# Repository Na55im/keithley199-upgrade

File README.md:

# Keithley 199 Digital Board Replacement

**Collaboration:** [keithley199-upgrade](https://github.com/Na55im/keithley199-upgrade) on GitHub (branch `main`).

This is an upgrade replacement for the digital control board on Keithley 199 multimeters.

The [Keithley 199](doc/k199_op_maint.pdf) is a digital multimeter built in the nineties. It is capable of current, voltage and resistance measurements and also provides a gpib interface for remote control.

These multimeters contains three electronic circuit boards, one which contains the analog circuitry, including analog signal conditioning and analog digital converter, a display board which contains the user interface, and a digital control board, with a processor who controls display, gpib interface and analog digital converter.

This repository contains hardware and software files needed to build a replacement of the digital control board.

# Features
- Voltage Measurement 0.3, 3, 30, 300 VDC/VAC 6.5 digits
- Current Measurement 30mA, 3A DC/AC,  6.5 digits
- Resistance Measurement 300-3GOhm, 6.5 digits, 4 wire.
- Arbitrary integration period
- SCPI interface
- Free Software

# Building the hardware 

The hardware files are in [Kicad](http://kicad-pcb.org/) format. Gerber files are (not yet) available.

# Building the software

The software was built with the [Microchip Toolchain](http://www.microchip.com/mplab/compilers). 

We use [Ceedling](http://www.throwtheswitch.org/ceedling/) for building and testing (but for comfort, [MPLABX](http://www.microchip.com/mplab/mplab-x-ide) files are available). 

In order to build the software, go to the root directory and do:

```
$rake release

```
Or to perform the unit tests:
```
$rake test:all
```

## Hardware

The hardware is pretty basic. It contains a pic32mx controller which do the heavy lifting. An ftdi chip provides an usb interface, while two open drain drivers controll the led displays. The external trigger input and output are connected to the microcontroller through the necessary input/output protection.

## Calibration

TODO

## Principles of Operation

The interesting part is the Control of the analog board. The analog board contains a series of switches that are controlled with a shift register. The adc conversion is performed with a discrete charge-balance adc which returns a pulse train with a pulse count proportional to the input voltage. The control of the adc is performed by the microcontroller in the digital board and should observe a precise timing in order to guarantee adc accuracy.

As shown in the figure above, the charge balance phase starts after the controller sends a start of conversion to the analog board. While the charge balance phase takes place, the controller counts the number of pulses it receives from the analog board. The analog board only send pulses on the up parts, thus the number of pulses is proportional to the charge acumulated. After exactly 16.66 msecs the controller sends an stop of conversion and the single slope phase starts, discharging the integrator. While discharge takes place, the controller counts the number of pulses received.

# Licence

```
 * Copyright (c) 2015, Diego F. Asanza. All rights reserved.
 *
 * This software is free software; you can redistribute it and/or
 * modify it under the terms of the GNU Lesser General Public
 * License as published by the Free Software Foundation; either
 * version 2.1 of the License, or (at your option) any later version.
 *
 * This library is distributed in the hope that it will be useful,
 * but WITHOUT ANY WARRANTY; without even the implied warranty of
 * MERCHANTABILITY or FITNESS FOR A PARTICULAR PURPOSE.  See the GNU
 * Lesser General Public License for more details.
 *
 * You should have received a copy of the GNU Lesser General Public
 * License along with this library; if not, write to the Free Software
 * Foundation, Inc., 51 Franklin Street, Fifth Floor, Boston,
 * MA 02110-1301  USA
 *
 ```

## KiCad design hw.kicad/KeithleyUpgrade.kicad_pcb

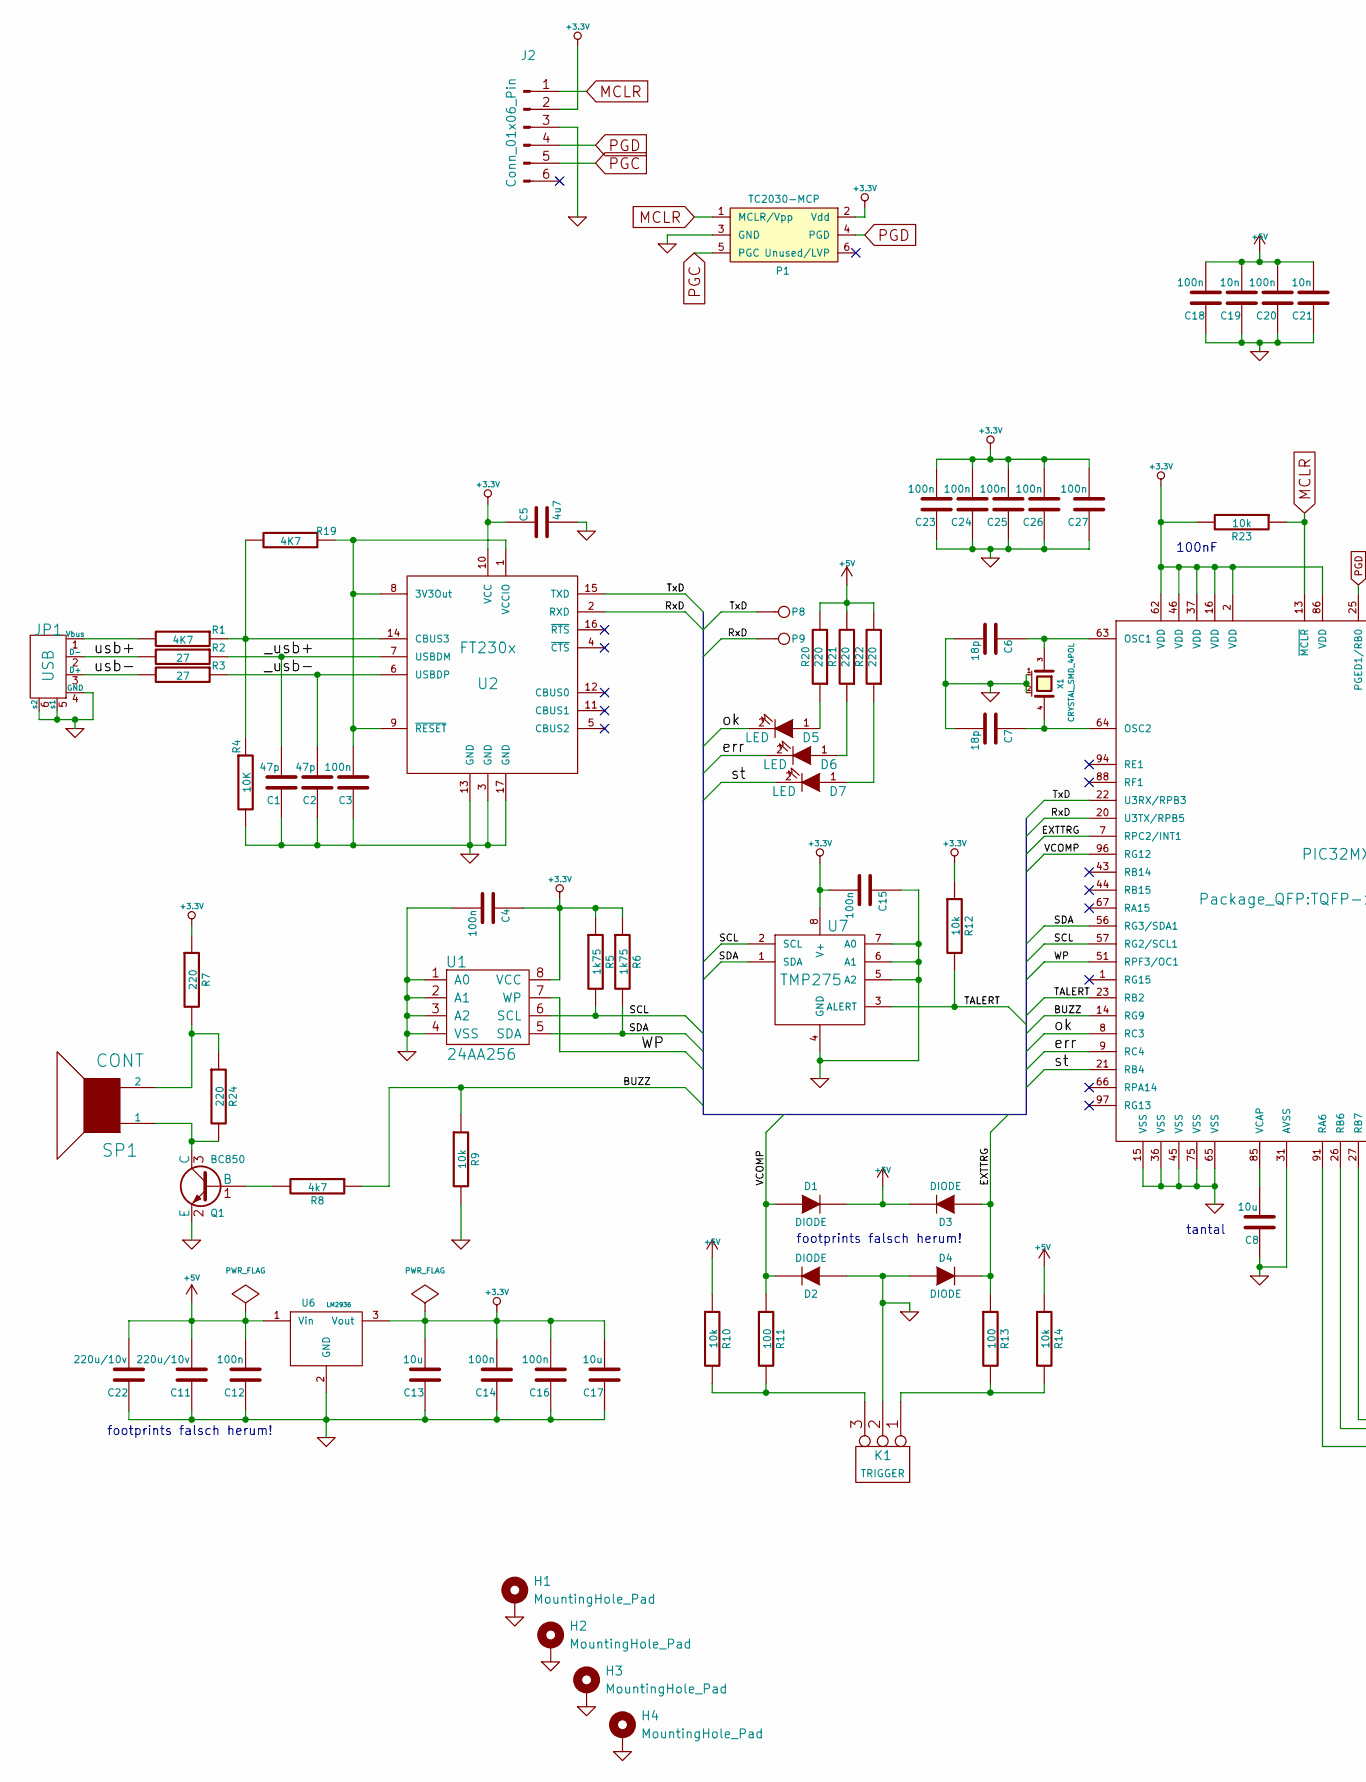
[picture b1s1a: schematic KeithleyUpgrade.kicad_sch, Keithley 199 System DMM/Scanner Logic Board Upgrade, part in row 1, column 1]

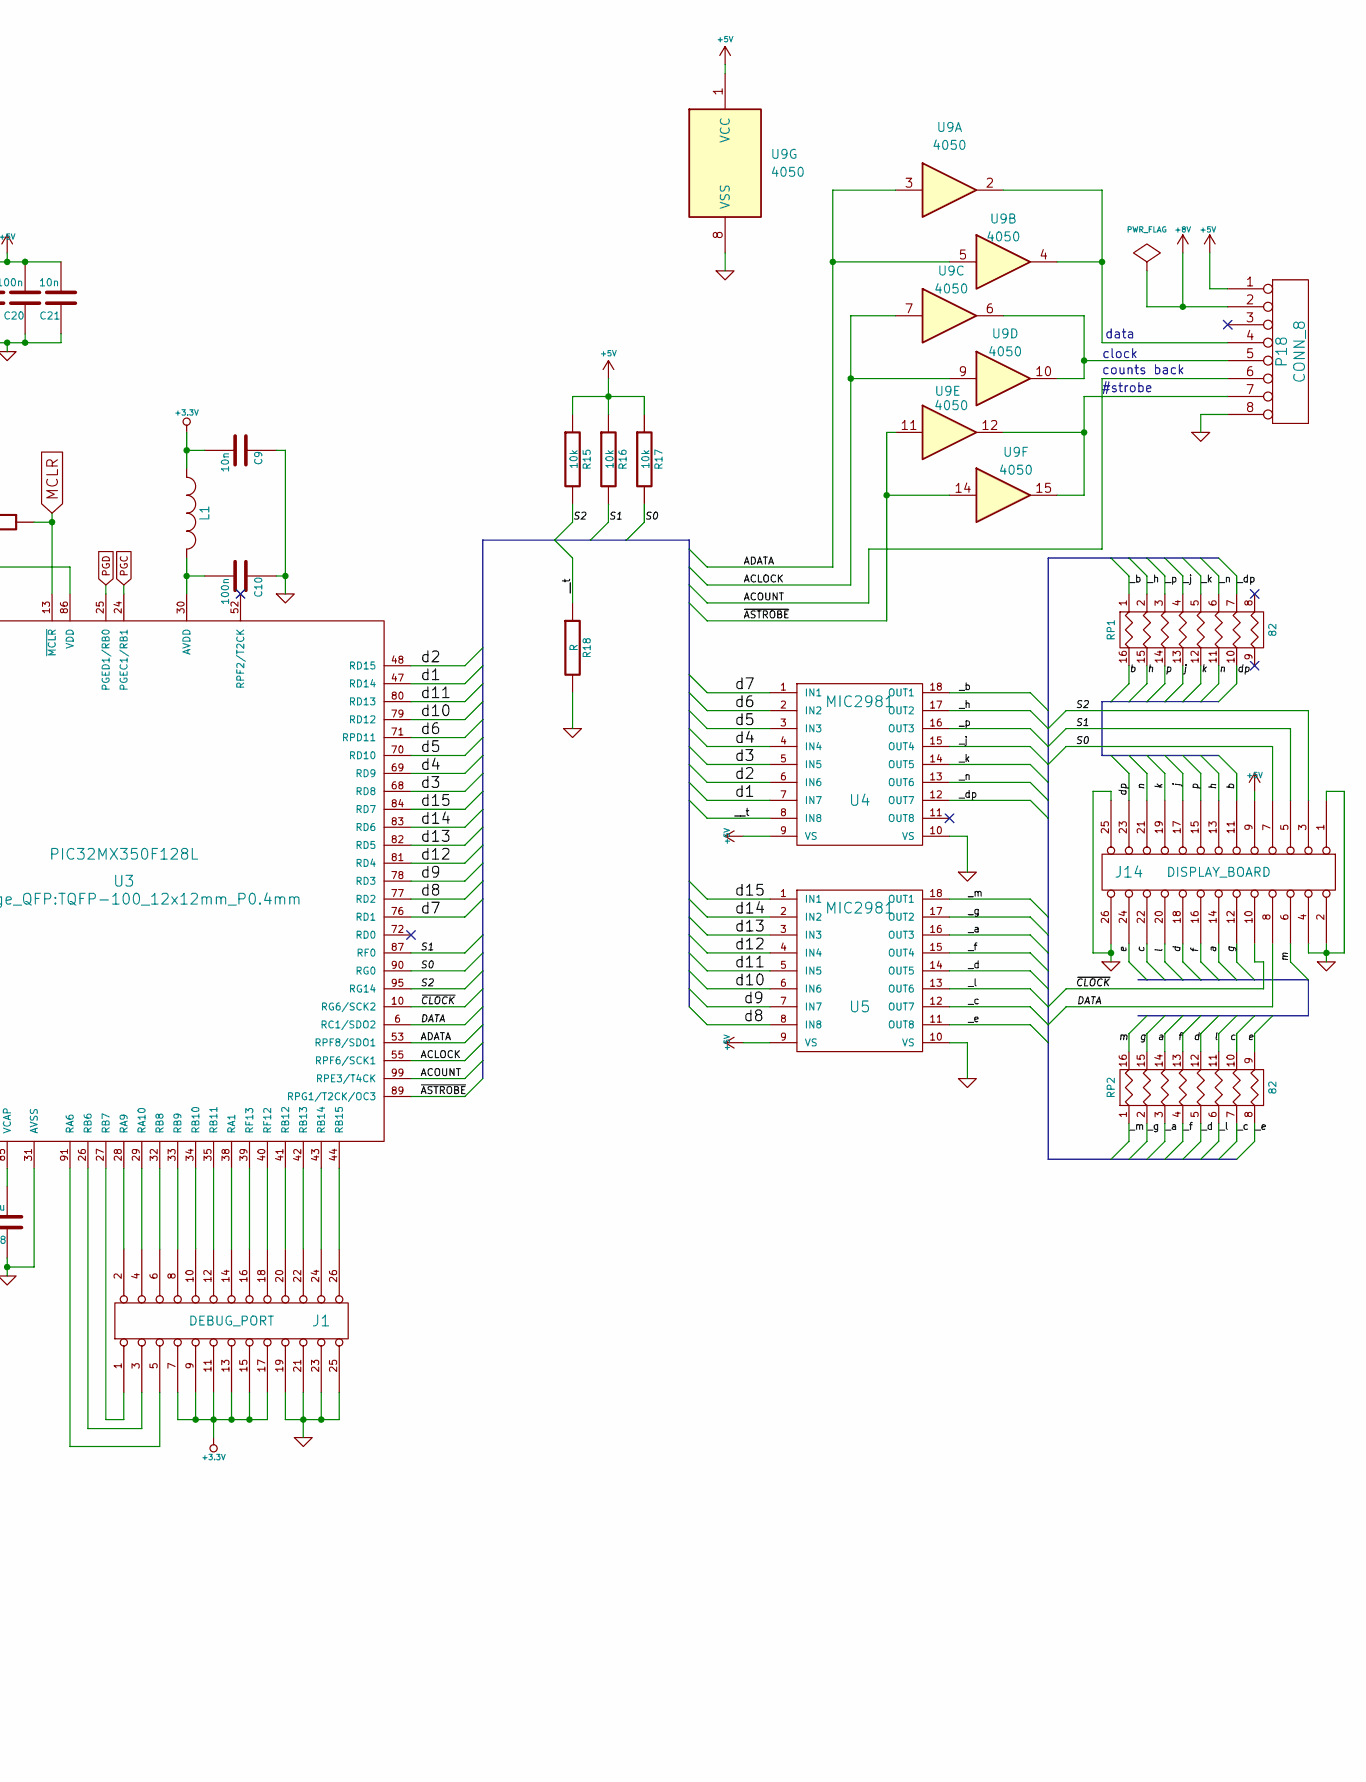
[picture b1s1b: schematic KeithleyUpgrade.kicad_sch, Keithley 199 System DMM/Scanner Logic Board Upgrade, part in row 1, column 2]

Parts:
C1, C2: 47p; C_0805_2012Metric_Pad1.18x1.45mm_HandSolder
C3, C4, C10, C12, C14, C15, C16, C18, C20: 100n; C_0805_2012Metric_Pad1.18x1.45mm_HandSolder
C5: 4u7; C_0805_2012Metric_Pad1.18x1.45mm_HandSolder
C6, C7: 18p; C_0805_2012Metric_Pad1.18x1.45mm_HandSolder
C8, C13, C17: 10u; C_0805_2012Metric_Pad1.18x1.45mm_HandSolder
C9, C19, C21: 10n; C_0805_2012Metric_Pad1.18x1.45mm_HandSolder
C11, C22: 220u/10v; CP_Elec_6.3x5.4
C23, C24, C25, C26, C27: 100n; C_0603_1608Metric
D1, D2, D3, D4: DIODE; D_SMA
D5, D6, D7: LED; LED_0805_2012Metric_Pad1.15x1.40mm_HandSolder
H1, H2, H3, H4: MountingHole_Pad; MountingHole_3.2mm_M3_Pad_Via
J1: DEBUG_PORT; PinHeader_2x13_P2.54mm_Vertical
J2: Conn_01x06_Pin; PinHeader_1x06_P2.54mm_Vertical
J14: DISPLAY_BOARD; PinHeader_2x13_P2.54mm_Vertical
JP1: USB; USB_B
K1: TRIGGER; bornier3
L1: L_1210_3225Metric
P1: TC2030-MCP; Tag-Connect_TC2030-IDC-NL_2x03_P1.27mm_Vertical
P8, P9: TP1; TestPoint_Pad_1.0x1.0mm
P18: CONN_8; PinHeader_1x08_P2.54mm_Vertical
Q1: BC850; SOT-23
R1: 4K7; C_0805_2012Metric_Pad1.18x1.45mm_HandSolder
R2, R3: 27; C_0805_2012Metric_Pad1.18x1.45mm_HandSolder
R4: 10K; C_0805_2012Metric_Pad1.18x1.45mm_HandSolder
R5, R6: 1k75; C_0805_2012Metric_Pad1.18x1.45mm_HandSolder
R7: 220; C_0805_2012Metric_Pad1.18x1.45mm_HandSolder
R8: 4k7; C_0805_2012Metric_Pad1.18x1.45mm_HandSolder
R9, R10, R12, R14, R15, R16, R17, R23: 10k; R_0805_2012Metric_Pad1.20x1.40mm_HandSolder
R11, R13: 100; R_0805_2012Metric_Pad1.20x1.40mm_HandSolder
R18: R; R_0805_2012Metric_Pad1.20x1.40mm_HandSolder
R19: 4K7; R_0805_2012Metric_Pad1.20x1.40mm_HandSolder
R20, R21, R22, R24: 220; R_0805_2012Metric_Pad1.20x1.40mm_HandSolder
RP1, RP2: 82; SO-16_5.3x10.2mm_P1.27mm
SP1: CONT; Elko_vert_DM14_RM5
U1: 24AA256; SOIC-8_3.9x4.9mm_P1.27mm
U2: FT230x; SSOP-16_5.3x6.2mm_P0.65mm
U3: PIC32MX350F128L; TQFP-100_12x12mm_P0.4mm
U4, U5: MIC2981; SOIC-18W_7.5x11.6mm_P1.27mm
U6: LM2936; TO-252-3_TabPin2
U7: TMP275; SOIC-8_3.9x4.9mm_P1.27mm
U9: 4050; SO-16_5.3x10.2mm_P1.27mm
X1: CRYSTAL_SMD_4POL; Crystal_SMD_5032-4Pin_5.0x3.2mm

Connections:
+3.3V: C4.1, C5.1, C9.2, C13.2, C14.2, C15.2, C16.2, C17.2, C23.2, C24.2, C25.2, C26.2, C27.2, J1.7, J1.9, J1.11, J1.13, J1.15, J1.17, J2.2, L1.1, P1.2 (Vdd), R5.1, R6.1, R7.1, R12.1, R23.2, U1.8 (VCC), U2.10 (VCC), U3.2 (VDD), U3.16 (VDD), U3.37 (VDD), U3.46 (VDD), U3.62 (VDD), U3.86 (VDD), U6.3 (Vout), U7.8 (V+)
+5V: C11.2, C12.2, C18.2, C19.2, C20.2, C21.2, C22.2, D1.2 (K), D3.2 (K), J14.9, P18.1, R10.1, R14.1, R15.1, R16.1, R17.1, R20.2, R21.2, R22.2, U4.9 (VS), U5.9 (VS), U6.1 (Vin), U9.1 (VCC)
+8V: P18.2
/ACLOCK: U3.55 (RPF6/SCK1), U9.7, U9.9
/ACOUNT: P18.6, U3.99 (RPE3/T4CK)
/ADATA: U3.53 (RPF8/SDO1), U9.3, U9.5
/BUZZ: R8.1, R9.1, U3.14 (RG9)
/DATA: J14.8, U3.6 (RC1/SDO2)
/EXTTRG: D3.1 (A), D4.2 (K), R13.1, U3.7 (RPC2/INT1)
/RxD: P9.1, U2.2 (RXD), U3.20 (U3TX/RPB5)
/S0: J14.7, R17.2, U3.90 (RG0)
/S1: J14.5, R16.2, U3.87 (RF0)
/S2: J14.3, R15.2, U3.95 (RG14)
/SCL: R5.2, U1.6 (SCL), U3.57 (RG2/SCL1), U7.2 (SCL)
/SDA: R6.2, U1.5 (SDA), U3.56 (RG3/SDA1), U7.1 (SDA)
/TALERT: R12.2, U3.23 (RB2), U7.3 (ALERT)
/TxD: P8.1, U2.15 (TXD), U3.22 (U3RX/RPB3)
/VCOMP: D1.1 (A), D2.2 (K), R11.1, U3.96 (RG12)
/WP: U1.7 (WP), U3.51 (RPF3/OC1)
/__t: R18.1, U4.8 (IN8)
/_a: RP2.3, U5.16 (OUT3)
/_b: RP1.1, U4.18 (OUT1)
/_c: RP2.7, U5.12 (OUT7)
/_d: RP2.5, U5.14 (OUT5)
/_dp: RP1.7, U4.12 (OUT7)
/_e: RP2.8, U5.11 (OUT8)
/_f: RP2.4, U5.15 (OUT4)
/_g: RP2.2, U5.17 (OUT2)
/_h: RP1.2, U4.17 (OUT2)
/_j: RP1.4, U4.15 (OUT4)
/_k: RP1.5, U4.14 (OUT5)
/_l: RP2.6, U5.13 (OUT6)
/_m: RP2.1, U5.18 (OUT1)
/_n: RP1.6, U4.13 (OUT6)
/_p: RP1.3, U4.16 (OUT3)
/_usb+: C1.2, R2.1, U2.7 (USBDM)
/_usb-: C2.2, R3.1, U2.6 (USBDP)
/a: J14.14, RP2.14 (R3)
/b: J14.11, RP1.16 (R1)
/c: J14.22, RP2.10 (R7)
/d: J14.18, RP2.12 (R5)
/d1: U3.47 (RD14), U4.7 (IN7)
/d2: U3.48 (RD15), U4.6 (IN6)
/d3: U3.68 (RD8), U4.5 (IN5)
/d4: U3.69 (RD9), U4.4 (IN4)
/d5: U3.70 (RD10), U4.3 (IN3)
/d6: U3.71 (RPD11), U4.2 (IN2)
/d7: U3.76 (RD1), U4.1 (IN1)
/d8: U3.77 (RD2), U5.8 (IN8)
/d9: U3.78 (RD3), U5.7 (IN7)
/d10: U3.79 (RD12), U5.6 (IN6)
/d11: U3.80 (RD13), U5.5 (IN5)
/d12: U3.81 (RD4), U5.4 (IN4)
/d13: U3.82 (RD5), U5.3 (IN3)
/d14: U3.83 (RD6), U5.2 (IN2)
/d15: U3.84 (RD7), U5.1 (IN1)
/dp: J14.23, RP1.10 (R7)
/e: J14.24 (P20), RP2.9 (R8)
/err: D6.2 (K), U3.9 (RC4)
/f: J14.16, RP2.13 (R4)
/g: J14.12, RP2.15 (R2)
/h: J14.13, RP1.15 (R2)
/j: J14.17, RP1.13 (R4)
/k: J14.19, RP1.12 (R5)
/l: J14.20, RP2.11 (R6)
/m: J14.6, RP2.16 (R1)
/n: J14.21, RP1.11 (R6)
/ok: D5.2 (K), U3.8 (RC3)
/p: J14.15, RP1.14 (R3)
/st: D7.2 (K), U3.21 (RB4)
/usb+: JP1.2 (D-), R2.2
/usb-: JP1.3 (D+), R3.2
/~ASTROBE: U3.89 (RPG1/T2CK/OC3), U9.11, U9.14
/~CLOCK: J14.10, U3.10 (RG6/SCK2)
GND: C1.1, C2.1, C3.1, C4.2, C5.2, C6.2, C7.2, C8.1, C9.1, C10.1, C11.1, C12.1, C13.1, C14.1, C15.1, C16.1, C17.1, C18.1, C19.1, C20.1, C21.1, C22.1, C23.1, C24.1, C25.1, C26.1, C27.1, D2.1 (A), D4.1 (A), H1.1, H2.1, H3.1, H4.1, J1.19, J1.21, J1.23, J1.25 (P24), J2.3, J14.1, J14.2, J14.4, J14.25 (P24), J14.26 (P22), JP1.4 (GND), JP1.5 (s1), JP1.6 (s2), K1.2 (PM), P1.3 (GND), P18.8, Q1.2 (E), R4.2, R9.2, R18.2, U1.1 (A0), U1.2 (A1), U1.3 (A2), U1.4 (VSS), U2.3 (GND), U2.13 (GND), U2.17 (GND), U3.15 (VSS), U3.31 (AVSS), U3.36 (VSS), U3.45 (VSS), U3.65 (VSS), U3.75 (VSS), U4.10 (VS), U5.10 (VS), U6.2 (GND), U7.4 (GND), U7.5 (A2), U7.6 (A1), U7.7 (A0), U9.8 (VSS), X1.1 (case), X1.2 (case)
MCLR: J2.1, P1.1 (MCLR/Vpp), R23.1, U3.13 (~MCLR)
unnamed: D5.1 (A), R20.1
unnamed: D6.1 (A), R21.1
unnamed: D7.1 (A), R22.1
unnamed: J1.1, U3.27 (RB7)
unnamed: J1.2, U3.28 (RA9)
unnamed: J1.3, U3.26 (RB6)
unnamed: J1.4, U3.29 (RA10)
unnamed: J1.5, U3.91 (RA6)
unnamed: J1.6, U3.32 (RB8)
unnamed: J1.8, U3.33 (RB9)
unnamed: J1.10, U3.34 (RB10)
unnamed: J1.12, U3.35 (RB11)
unnamed: J1.14, U3.38 (RA1)
unnamed: J1.16, U3.39 (RF13)
unnamed: J1.18, U3.40 (RF12)
unnamed: JP1.1 (Vbus), R1.2
unnamed: K1.1, R13.2, R14.2
unnamed: K1.3, R10.2, R11.2
unnamed: P18.4, U9.2, U9.4
unnamed: P18.5, U9.6, U9.10
unnamed: P18.7, U9.12, U9.15
unnamed: Q1.1 (B), R8.2
unnamed: Q1.3 (C), R24.2, SP1.1
unnamed: R7.2, R24.1, SP1.2
unnamed: C3.2, R19.1, U2.1 (VCCIO), U2.8 (3V3Out), U2.9 (~RESET)
unnamed: R1.1, R4.1, R19.2, U2.14 (CBUS3)
unnamed: C10.2, L1.2, U3.30 (AVDD)
unnamed: C6.1, U3.63 (OSC1), X1.3
unnamed: C7.1, U3.64 (OSC2), X1.4
unnamed: J1.20, U3.41 (RB12)
unnamed: J1.22, U3.42 (RB13)
unnamed: J1.24 (P20), U3.43 (RB14)
unnamed: J1.26 (P22), U3.44 (RB15)
unnamed: C8.2, U3.85 (VCAP)
PGC: J2.5, P1.5 (PGC), U3.24 (PGEC1/RB1)
PGD: J2.4, P1.4 (PGD), U3.25 (PGED1/RB0)

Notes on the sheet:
100nF
clock
tantal
counts back
#strobe
footprints falsch herum!
data

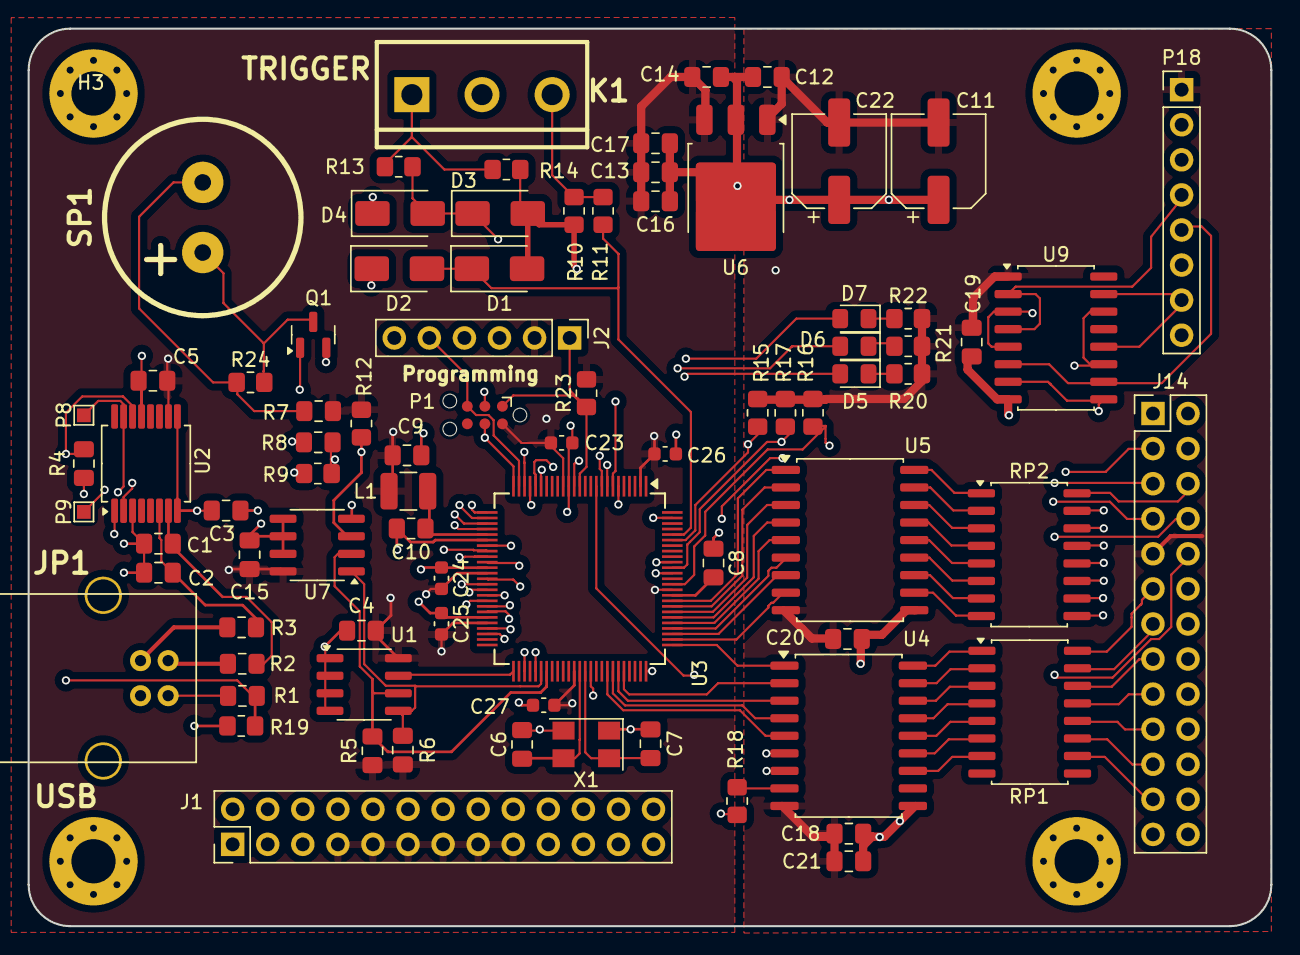
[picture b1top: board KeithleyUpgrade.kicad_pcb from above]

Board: 4 copper layers, 90.0 x 65.0 mm, 85 parts (0 on the bottom side), 111 nets.

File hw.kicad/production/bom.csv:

Designator,Footprint,Quantity,Value,LCSC Part #
"C1, C2",0805,2,47p,
"C10, C12, C14, C15, C16, C18, C20, C3, C4",0805,9,100n,
"C11, C22",CP_Elec_6.3x5.4,2,220u/10v,
"C13, C17, C8",0805,3,10u,
"C19, C21, C9",0805,3,10n,
"C23, C24, C25, C26, C27",0603,5,100n,
C5,0805,1,4u7,
"C6, C7",0805,2,18p,
"D1, D2, D3, D4",D_SMA,4,DIODE,
"D5, D6, D7",0805,3,LED,
J1,PinHeader_2x13_P2.54mm_Vertical,1,DEBUG_PORT,
J14,PinHeader_2x13_P2.54mm_Vertical,1,DISPLAY_BOARD,
J2,PinHeader_1x06_P2.54mm_Vertical,1,Conn_01x06_Pin,
JP1,USB_B,1,USB,
K1,bornier3,1,TRIGGER,
L1,1210,1,~,
P1,Tag-Connect_TC2030-IDC-NL_2x03_P1.27mm_Vertical,1,TC2030-MCP,
P18,PinHeader_1x08_P2.54mm_Vertical,1,CONN_8,
"P8, P9",TestPoint_Pad_1.0x1.0mm,2,TP1,
Q1,SOT-23,1,BC850,
"R1, R19, R8",0805,3,4K7,
"R10, R12, R14, R15, R16, R17, R23, R4, R9",0805,9,10k,
"R11, R13",0805,2,100,
R18,0805,1,R,
"R2, R3",0805,2,27,
"R20, R21, R22, R24, R7",0805,5,220,
"R5, R6",0805,2,1k75,
"RP1, RP2",SO-16_5.3x10.2mm_P1.27mm,2,82,
SP1,Elko_vert_DM14_RM5,1,CONT,
U1,SOIC-8_3.9x4.9mm_P1.27mm,1,24AA256,
U2,SSOP-16_5.3x6.2mm_P0.65mm,1,FT230x,
U3,TQFP-100_12x12mm_P0.4mm,1,PIC32MX350F128L,
"U4, U5",SOIC-18W_7.5x11.6mm_P1.27mm,2,MIC2981,
U6,TO-252-3_TabPin2,1,LM2936,
U7,SOIC-8_3.9x4.9mm_P1.27mm,1,TMP275,
U9,SO-16_5.3x10.2mm_P1.27mm,1,4050,
X1,Crystal_SMD_5032-4Pin_5.0x3.2mm,1,CRYSTAL_SMD_4POL,
